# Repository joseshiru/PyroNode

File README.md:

# PyroNode

**PyroNode** is an open-source ESP32-based control system designed to manage multiple outputs, monitor temperature, and provide robust control over external devices. Originally built for automotive applications as a cost-effective alternative to a PMU (Power Management Unit) or aftermarket ECU, PyroNode has proven its versatility and can be adapted for various other projects, such as home automation or even controlling a **coffee roaster**.

## Features

- **ESP32-based system**: Powerful microcontroller with Wi-Fi and Bluetooth capabilities.
- **8 MOSFET-controlled outputs**: Manage and control up to 8 high-power circuits.
- **Overload protection**: Ensures safety and reliability in high-power environments.
- **Temperature monitoring**: Supports 2 thermocouples via **MAX6675K** and other temperature sensors like **MAX31855EASA**.
- **Waterproof connectors**: Ideal for harsh environments such as automotive, outdoor, or industrial applications.
- **Optoisolated inputs**: Protects the system from electrical noise and interference.
- **Modular MOSFET satellites**: Easy expansion and replacement of MOSFET modules.
- **Flexible usage**: Designed initially for automotive use but adaptable to many applications, including industrial controls, environmental monitoring, or DIY home projects.

## Applications

While PyroNode was initially created for controlling circuits in an automotive environment (like a PMU without the expense of aftermarket systems), it can be utilized in a wide range of other scenarios:

- **Automotive**: Act as a PMU to control different car subsystems.
- **Home automation**: Manage lighting, HVAC, or any other electronic devices.
- **Coffee roasting**: Use the temperature sensors and output controls to monitor and adjust a coffee roaster in real-time.
- **Industrial automation**: Control machines and monitor temperature in industrial settings.
- **Smart gardening**: Automate watering systems and monitor environmental conditions.

## Project Breakdown

### Hardware Overview
- **MOSFET Modules**: Utilize **PSMN013-30MLC MOSFETs** for high-efficiency switching and control of the 8 output channels.
- **Power Supply**: Uses an **LD1085D2T33 voltage regulator** to provide a stable 3.3V power supply.
- **Temperature Monitoring**: Equipped with **2 thermocouples via MAX6675K** for accurate temperature measurements, expandable with additional sensors like the **MAX31855EASA**.
- **Waterproof Connectors**: For safe usage in outdoor or automotive applications.
- **Optoisolation**: Provides electrical isolation to protect the ESP32 from spikes or noise in the connected circuits.
- **Modular Design**: MOSFET satellite modules can be easily expanded or swapped for different configurations.

### Software Overview

The software is built using the **Arduino IDE** for the ESP32 platform. A basic example of controlling the MOSFETs is included in the `main.cpp` file. The example alternates turning on and off the 8 MOSFET outputs with a delay of 1 second.

```cpp
#include <Arduino.h>

int MOSFET0_PIN = 13;
int MOSFET1_PIN = 14;
int MOSFET2_PIN = 27;
int MOSFET3_PIN = 26;
int MOSFET4_PIN = 25;
int MOSFET5_PIN = 21;
int MOSFET6_PIN = 22;
int MOSFET7_PIN = 23;

void setup() {
  pinMode(MOSFET0_PIN, OUTPUT);
  pinMode(MOSFET1_PIN, OUTPUT);
  pinMode(MOSFET2_PIN, OUTPUT);
  pinMode(MOSFET3_PIN, OUTPUT);
  pinMode(MOSFET4_PIN, OUTPUT);
  pinMode(MOSFET5_PIN, OUTPUT);
  pinMode(MOSFET6_PIN, OUTPUT);
  pinMode(MOSFET7_PIN, OUTPUT);
}

void loop() {
  digitalWrite(MOSFET0_PIN, HIGH);
  digitalWrite(MOSFET1_PIN, HIGH);
  digitalWrite(MOSFET2_PIN, HIGH);
  digitalWrite(MOSFET3_PIN, HIGH);
  digitalWrite(MOSFET4_PIN, HIGH);
  digitalWrite(MOSFET5_PIN, HIGH);
  digitalWrite(MOSFET6_PIN, HIGH);
  digitalWrite(MOSFET7_PIN, HIGH);
  delay(1000);  
  digitalWrite(MOSFET0_PIN, LOW);
  digitalWrite(MOSFET1_PIN, LOW);
  digitalWrite(MOSFET2_PIN, LOW);
  digitalWrite(MOSFET3_PIN, LOW);
  digitalWrite(MOSFET4_PIN, LOW);
  digitalWrite(MOSFET5_PIN, LOW);
  digitalWrite(MOSFET6_PIN, LOW);
  digitalWrite(MOSFET7_PIN, LOW);
  delay(1000); 
}

```
## License

This project is licensed under the **Creative Commons Attribution-NonCommercial 4.0 International (CC BY-NC 4.0)** license.

- **Free for personal and non-commercial use.**
- **Credits: Build by Jose Zuniga Marin.**
- **For commercial use, please contact hello@malecu.eu.**

You can read the full license [here](https://creativecommons.org/licenses/by-nc/4.0/).

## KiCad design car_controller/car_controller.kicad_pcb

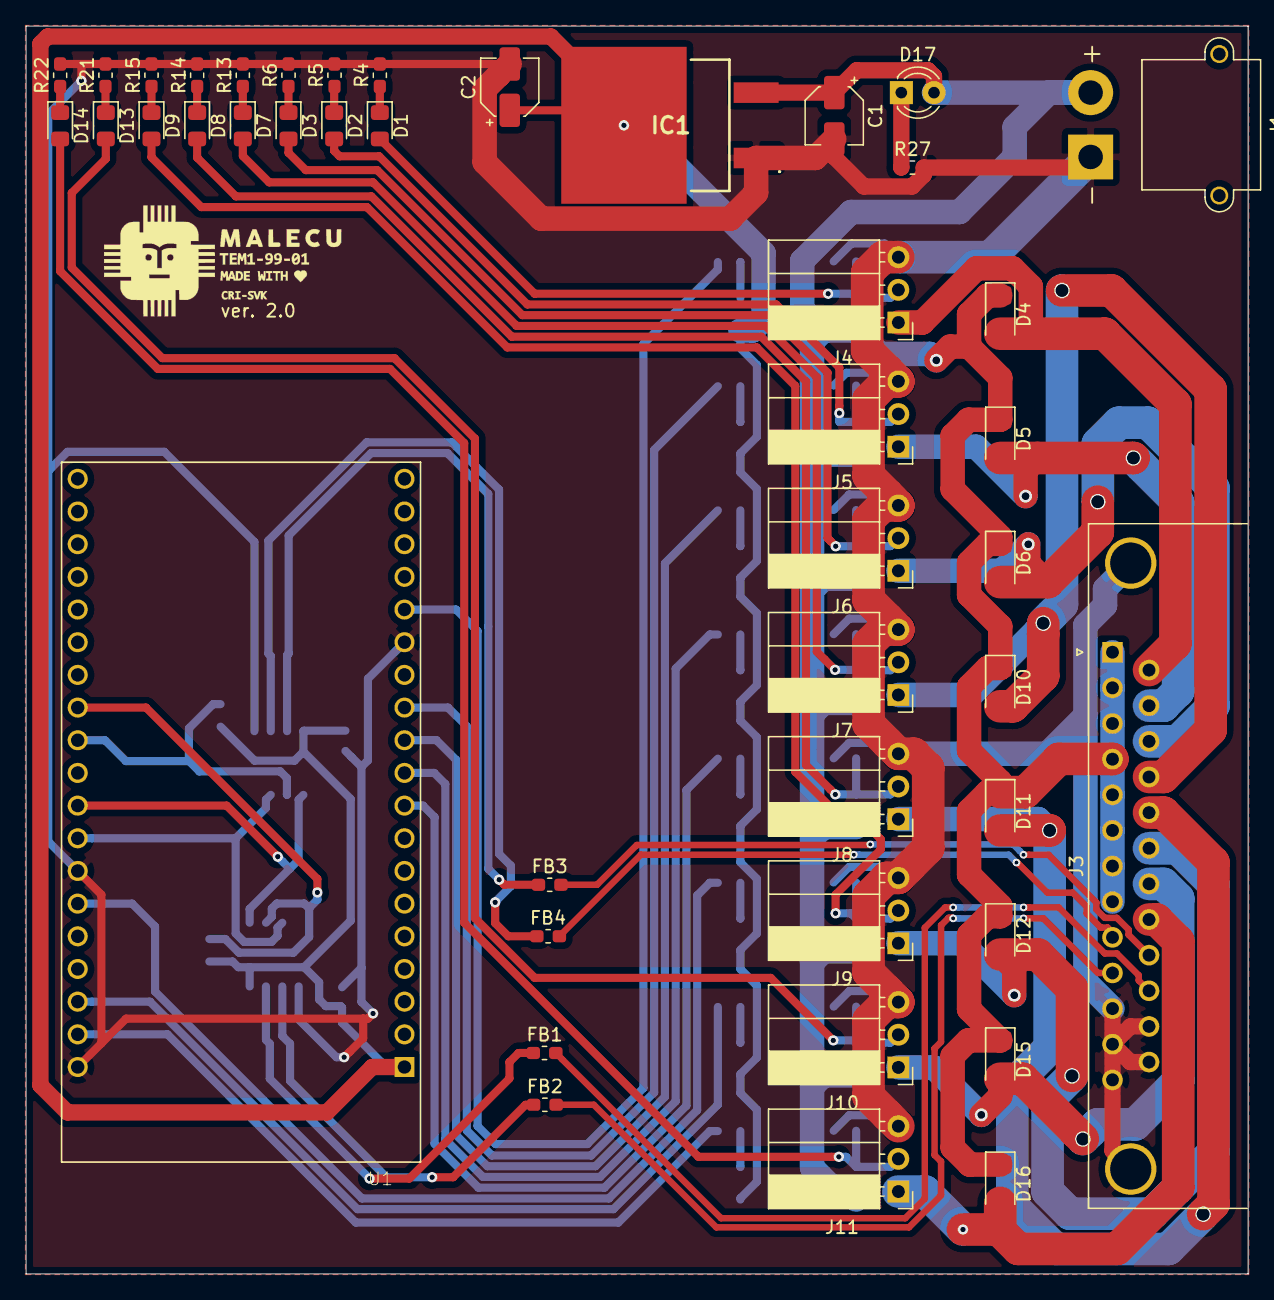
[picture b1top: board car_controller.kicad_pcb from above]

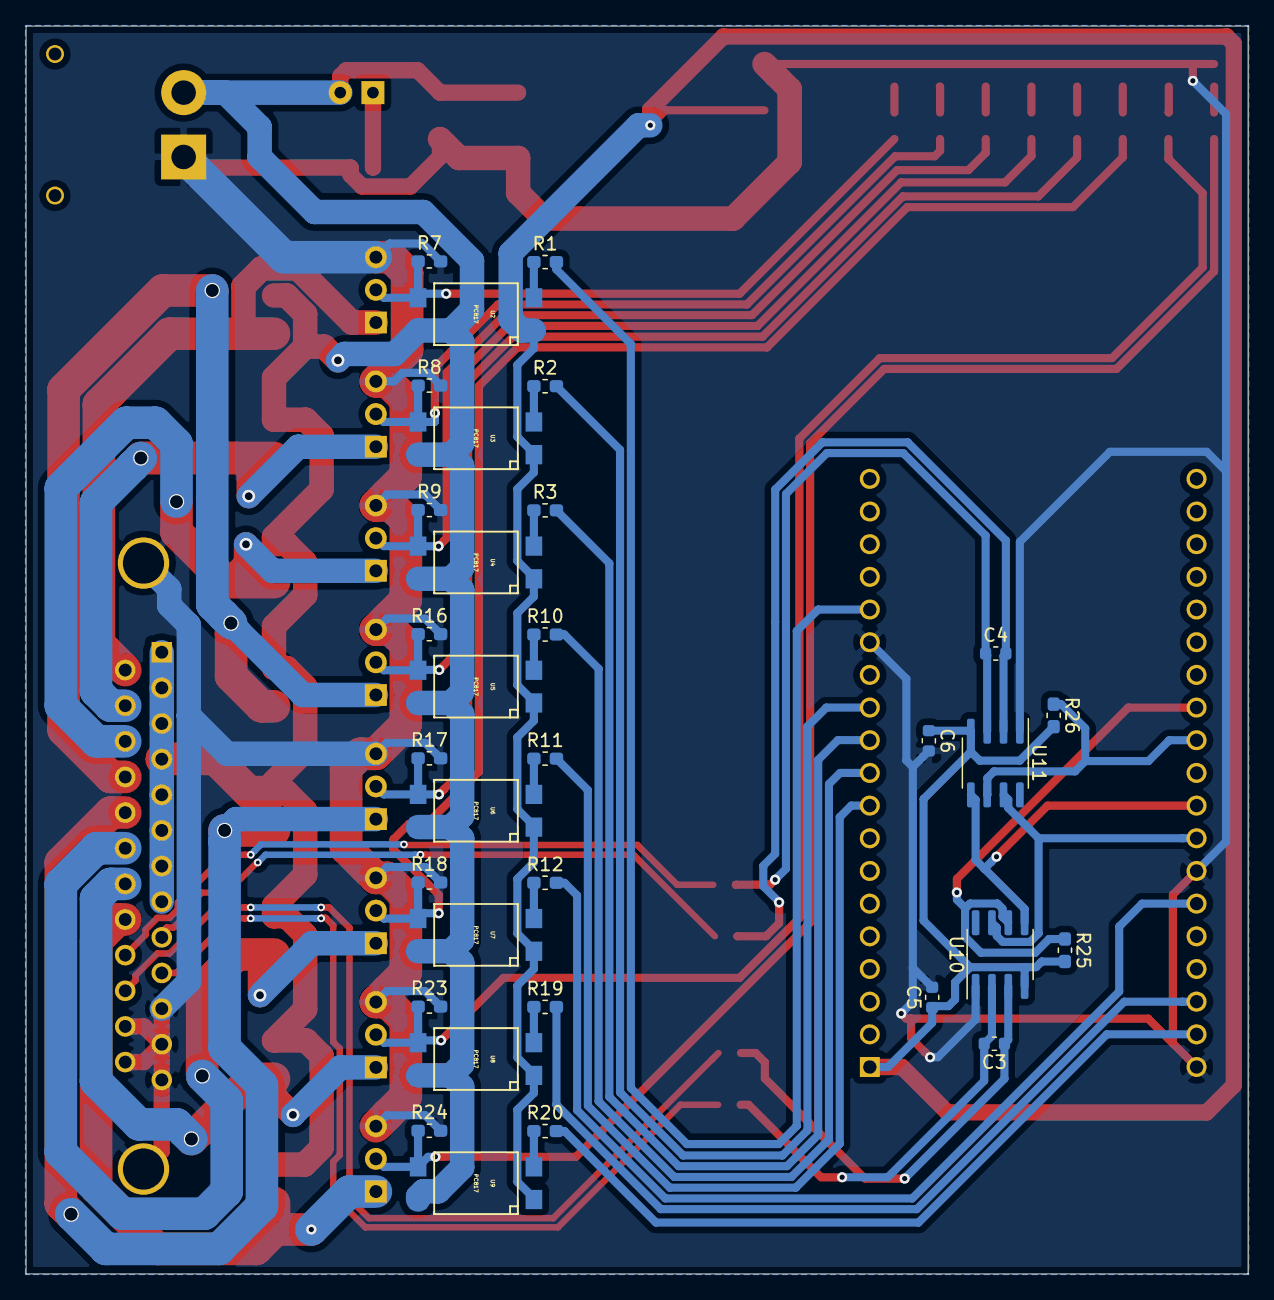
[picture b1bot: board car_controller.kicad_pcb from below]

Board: 2 copper layers, 95.0 x 97.0 mm, 76 parts (32 on the bottom side), 56 nets.

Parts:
C1, C2: 10µF; CP_Elec_4x5.3
C3, C4: 10nF; C_0603_1608Metric
C5, C6: 100nF; C_0603_1608Metric
D1, D2, D3, D7, D8, D9, D13, D14: LED; LED_0805_2012Metric_Pad1.15x1.40mm_HandSolder
D4, D5, D6, D10, D11, D12, D15, D16: D; D_1206_3216Metric_Pad1.42x1.75mm_HandSolder
D17: PWR_LED; LED_D3.0mm
FB1, FB2, FB3, FB4: 470Ω; L_0603_1608Metric_Pad1.05x0.95mm_HandSolder
IC1: LD1085D2T33R
J1: POWER_IN; AMASS_XT30PW-M_1x02_P2.50mm_Horizontal
J3: DB25_Female_MountingHoles; DSUB-25_Female_Horizontal_P2.77x2.84mm_EdgePinOffset7.70mm_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
J4, J5, J6, J7, J8, J9, J10, J11: DGS_F; PinSocket_1x03_P2.54mm_Horizontal
R1, R2, R3, R10, R11, R12, R19, R20: 120R; R_0603_1608Metric_Pad1.05x0.95mm_HandSolder
R4, R5, R6, R13, R14, R15, R21, R22, R27: 1k; R_0603_1608Metric_Pad1.05x0.95mm_HandSolder
R7, R8, R9, R16, R17, R18, R23, R24: 47k; R_0603_1608Metric_Pad1.05x0.95mm_HandSolder
R25, R26: 10k; R_0603_1608Metric_Pad1.05x0.95mm_HandSolder
U1: ESP32-DEVKITC-32D; MODULE_ESP32-DEVKITC-32D
U2, U3, U4, U5, U6, U7, U8, U9: PC817; OPTO-SMD4
U10, U11: MAX31855EASA; SOIC-8_3.9x4.9mm_P1.27mm

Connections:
+3V3: C2.1, C5.1, C6.1, IC1.4, R25.2, R26.2, U1.1, U2.1, U3.1, U4.1, U5.1, U6.1, U7.1, U8.1, U9.1, U10.4, U11.4
+12V: C1.1, D4.1, D5.1, D6.1, D10.1, D11.1, D12.1, D15.1, D16.1, D17.2, IC1.3, J1.2, J3.1, J3.2, J3.3, J3.4, J3.5, J3.6, J3.7, J3.8, U2.4, U3.4, U4.4, U5.4, U6.4, U7.4, U8.4, U9.4
/CON_0: R1.2, U1.15
/CON_1: R2.2, U1.12
/CON_2: R3.2, U1.11
/CON_3: R10.2, U1.10
/CON_4: R11.2, U1.9
/CON_5: R12.2, U1.25
/CON_6: R19.2, U1.22
/CON_7: R20.2, U1.21
/LOAD_0: D4.2, J3.14, J4.1
/LOAD_1: D5.2, J3.15, J5.1
/LOAD_2: D6.2, J3.16, J6.1
/LOAD_3: D10.2, J3.17, J7.1
/LOAD_4: D11.2, J3.18, J8.1
/LOAD_5: D12.2, J3.19, J9.1
/LOAD_6: D15.2, J3.20, J10.1
/LOAD_7: D16.2, J3.21, J11.1
/SPI_CS_0: R25.1, U1.31, U10.6
/SPI_CS_1: R26.1, U1.30, U11.6
/SPI_MISO: U1.27, U10.7, U11.7
/SPI_SCK: U1.28, U10.5, U11.5
/T_0+: FB1.2, J3.23
/T_0-: FB2.2, J3.10
/T_1+: FB3.2, J3.22
/T_1-: FB4.2, J3.9
GND: C1.2, C2.2, C5.2, C6.2, IC1.1, J1.1, J3.0, J3.11, J3.12, J3.13, J3.24, J3.25, J4.3, J5.3, J6.3, J7.3, J8.3, J9.3, J10.3, J11.3, R4.2, R5.2, R6.2, R7.2, R8.2, R9.2, R13.2, R14.2, R15.2, R16.2, R17.2, R18.2, R21.2, R22.2, R23.2, R24.2, R27.2, U1.14, U1.20, U1.26, U10.1, U11.1
unnamed: C3.1, FB1.1, U10.3
unnamed: C3.2, FB2.1, U10.2
unnamed: C4.1, FB3.1, U11.3
unnamed: C4.2, FB4.1, U11.2
unnamed: D1.1, R4.1
unnamed: D1.2, J4.2, R7.1, U2.3
unnamed: D2.1, R5.1
unnamed: D2.2, J5.2, R8.1, U3.3
unnamed: D3.1, R6.1
unnamed: D3.2, J6.2, R9.1, U4.3
unnamed: D7.1, R13.1
unnamed: D7.2, J7.2, R16.1, U5.3
unnamed: D8.1, R14.1
unnamed: D8.2, J8.2, R17.1, U6.3
unnamed: D9.1, R15.1
unnamed: D9.2, J9.2, R18.1, U7.3
unnamed: D13.1, R21.1
unnamed: D13.2, J10.2, R23.1, U8.3
unnamed: D14.1, R22.1
unnamed: D14.2, J11.2, R24.1, U9.3
unnamed: D17.1, R27.1
unnamed: R1.1, U2.2
unnamed: R2.1, U3.2
unnamed: R3.1, U4.2
unnamed: R10.1, U5.2
unnamed: R11.1, U6.2
unnamed: R12.1, U7.2
unnamed: R19.1, U8.2
unnamed: R20.1, U9.2

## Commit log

2024-10-07 Removed unused files
2024-10-08 Update contact email. Add PCB photo
2024-10-08 Add PCB image to Readme file
